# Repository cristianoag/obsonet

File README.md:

# Obsonet Reloaded

This is the GitHub repository to host all source files for the Obsonet Reloaded. 

The ObsoNET is the first network card created for the MSX. In 2004, the hardware designer Daniel Berdugo and software developer Nestor Soriano joined forces to create a cartridge to bring ETHERNET standard to the MSX line of computers. 

The cartridge is based on the Realtek RTL8019AS chip and uses a flash memory to host and execute a BIOS that allows the use of network commands from the Nextor operating system (compatible with MSXDOS). An EPROM stores basic configuration data for the RTL8019AS chip and a side connector is used to plug a network cable to your MSX. A GAL16VB is used to implement the logic required to activate and expose the cartridge to the computer.

The original version of the Obsonet was designed to fit a standard Konami cartridge case. The goal of this project is to create a new version of the cartridge that fits the standard Patola cartridge case available in Brazil as well as the standard Konami cases available from multiple vendors WW.

## Hardware 

### PCB

The files required to build the original version of the Obsonet are available [https://github.com/msx-solis/obsonet](here). You can download the gerber files and order from any PCB manufacturer.

I have created another version of the PCB that I called Obsonet Reloaded. The goal was to have the board fitting the standard Patola cartridge cases available in Brazil as well as the standard Konami cases available from multiple vendors WW.

|Front Side|Back Side|
|----------|---------|
|||
|||

### Bill of Materials

[Obsonet Reloaded Interactive BOM](https://htmlpreview.github.io/?https://github.com/cristianoag/obsonet/blob/main/hardware/bom/ibom.html)

| Reference | Value    | Description         | Package                  | Qtd | Link                                                                                         |
|-----------|----------|---------------------|---------------------------|-----|----------------------------------------------------------------------------------------------|
| C1-C4     | 100nF    | C-EUC1206K          | C1206                     | 4   | [Ali Express](https://s.click.aliexpress.com/e/_DmIukoX)                                    |
| C6        | 100 uF   | CPOL-EUE2.5-5       | E2.5-5                    | 1   | [Ali Express](https://s.click.aliexpress.com/e/_DmAGIvh)                                    |
| C7-C10    | 10nF     | C-EU050-030X075     | C050-030X075              | 4   | [Ali Express](https://s.click.aliexpress.com/e/_Dmqpgbd)                                    |
| CON2      | RJ45_F   | 555153-1             | 555153-1                  | 1   | [Ali Express](https://s.click.aliexpress.com/e/_c3jkvfpj) |
| IC1       | M29F400M | M29F400M             | SO44                      | 1   | [Ali Express](https://s.click.aliexpress.com/e/_c3iPiyOp)                                    |
| IC2       | 93C46_SOIC | AT93CX6SOIC08      | SOIC8 (you only need one DIP8 or SOIC8) | 1*  | [Ali Express](https://s.click.aliexpress.com/e/_De08kgX)                                    |
| IC3       | 74LS133  | 74LS133             | DIP16                     | 1   | [Ali Express](https://s.click.aliexpress.com/e/_c3DB6u1B)                                    |
| IC4       | RTL8019AS | RTL8019AS           | RTL8019AS                  | 1   | [Ali Express](https://s.click.aliexpress.com/e/_c3tW51wN)                                    |
| IC5       | 93C46_DIL | AT93CX6DIP8         | DIP8 (you only need one DIP8 or SOIC8) | 1*  |                                                                                              |
| IC6       | GAL16V8D | GAL16V8D             | DIP20                     | 1   | [Ali Express](https://s.click.aliexpress.com/e/_DB7dHhf)                                    |
| LED1      | Green    | Led 3mm              | LED3MM                    | 1   | [Ali Express](https://s.click.aliexpress.com/e/_DeGtXFv)                                    |
| LED2      | Orange   | Led 3mm              | LED3MM                    | 1   | [Ali Express](https://s.click.aliexpress.com/e/_DeGtXFv)                                    |
| Q1        | 20MHz    | HC49GW/HC49U         | HC49GW/J (or you can adapt the conventional HC49U) | 1   | [Ali Express](https://s.click.aliexpress.com/e/_c3AIkohX)                                    |
| R1,R4,R5  | 11K      | R-EU_R1206          | R1206                     | 3   | [Ali Express](https://s.click.aliexpress.com/e/_DF7KTEP)                                    |
| R2,R3     | 300R     | R-EU_R1206          | R1206                     | 2   | [Ali Express](https://s.click.aliexpress.com/e/_DF7KTEP)                                    |
| R6        | 27K      | R-EU_R1206          | R1206                     | 1   | [Ali Express](https://s.click.aliexpress.com/e/_DF7KTEP)                                    |
| R7        | 200R     | R-EU_R1206          | R1206                     | 1   | [Ali Express](https://s.click.aliexpress.com/e/_DF7KTEP)                                    |
| SW1       | SWITCH   | Microswitch 6×6     | 6×6 microswitch SMD       | 1   | [Ali Express](https://s.click.aliexpress.com/e/_DFJZR15)                                    |
| TF1       | 20F001N  | 20F001N             | DIL16/12                  | 1   | [Ali Express](https://s.click.aliexpress.com/e/_c3lk5as5)                                    |

## Software

On this repo you can find all software required to build and use the Obsonet Reloaded. There are also binary files with fixes for small issues we found during the project.

### BIOS

The BIOS is the software that runs on the flash memory of the cartridge. It is responsible for initializing the hardware and providing a set of functions to the Nextor operating system.

## Resources

I wrote an article providing more information on how to acquire components and build the new version of the cartridge. You can check it on my blog at [http://www.theretrohacker.com/2022/11/04/the-obsonet-cartridge-for-the-msx/](http://www.theretrohacker.com/2022/11/04/the-obsonet-cartridge-for-the-msx/).

I also have a video in Portuguese showing the board, software, issues we faced during the remodel project as well as showing how to use it to download and use software on your MSX. Please check it at [https://www.youtube.com/watch?v=Ph_3VFheo2I](https://www.youtube.com/watch?v=Ph_3VFheo2I)

## License

This work is licensed under a [Creative Commons Attribution-NonCommercial-ShareAlike 4.0 International License](http://creativecommons.org/licenses/by-nc-sa/4.0/).

Original version build by Daniel Berdugo and Nestor Soriano. Reloaded version by The Retro Hacker. 

* If you remix, transform, or build upon the material, you must distribute your contributions under the same license as the original.
* You may not use the material for commercial purposes.
* You must give appropriate credit, provide a link to the license, and indicate if changes were made. You may do so in any reasonable manner, but not in any way that suggests the licensor endorses you or your use.

**ATTENTION**

This project was made for the retro community and not for commercial purposes. So only retro hardware forums and individual people can build this project.

THE SALE OF ANY PART OF THIS PROJECT WITHOUT EXPRESS AUTHORIZATION IS PROHIBITED!

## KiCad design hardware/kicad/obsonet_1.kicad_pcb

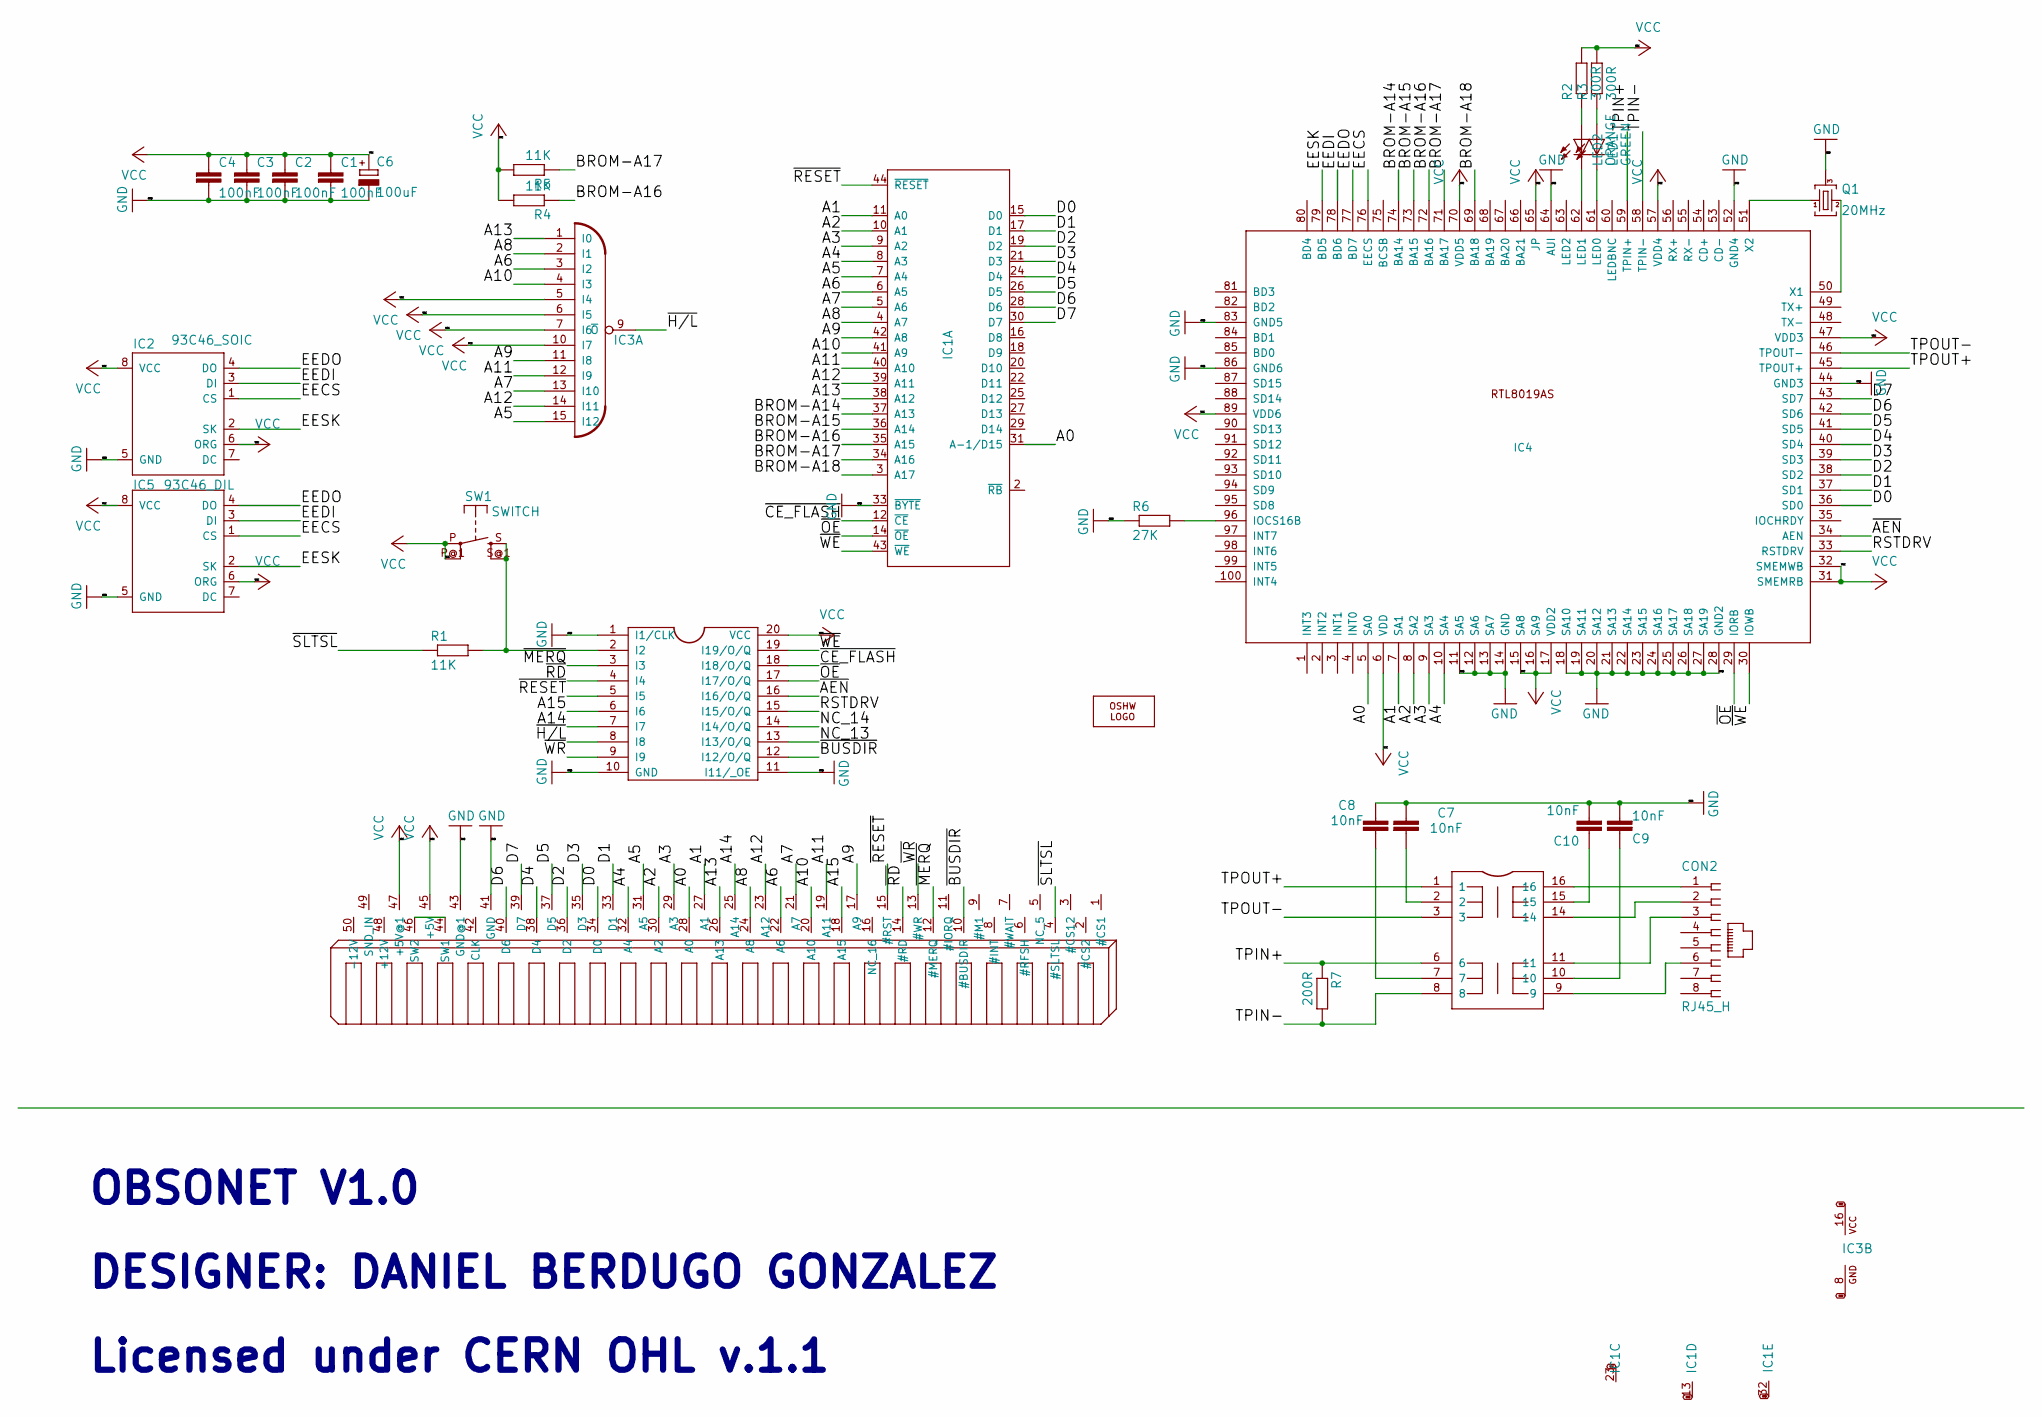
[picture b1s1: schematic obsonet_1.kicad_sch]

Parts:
C1, C2, C3, C4: 100nF; C1206K
C6: 100uF; E2,5-5
C7, C8, C9, C10: 10nF; C050-030X075
CON1: CART_BOARD; MSXCART
CON2: RJ45_H; 555153-1
IC1: M29F400M; SO44
IC2: 93C46_SOIC; SOIC8
IC3: 74HC133; DIP16
IC4: RTL8019AS
IC5: 93C46_DIL; DIP8
IC6: GAL16V8D; DIL20_SQUARE_1.5MM
LED1: GREEN; LED3MM
LED2: ORANGE; LED3MM
LOGO1: OSHW_LOGO_FILLX0500-NT; OSHW_FILLX500_NOTEXT
Q1: 20MHz; HC49GW
R1, R4, R5: 11K; R1206
R2, R3: 300R; R1206
R6: 27K; R1206
R7: 200R; R1206
SW1: SWITCH; MICROPULSADOR_6X6
TF1: 20F001N; DIL16_12

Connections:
/A0: CON1.28 (A0), IC1.31 (A-1/D15), IC4.5 (SA0)
/A1: CON1.27 (A1), IC1.11 (A0), IC4.7 (SA1)
/A2: CON1.30 (A2), IC1.10 (A1), IC4.8 (SA2)
/A3: CON1.29 (A3), IC1.9 (A2), IC4.9 (SA3)
/A4: CON1.32 (A4), IC1.8 (A3), IC4.10 (SA4)
/A5: CON1.31 (A5), IC1.7 (A4), IC3.15 (I12)
/A6: CON1.22 (A6), IC1.6 (A5), IC3.3 (I2)
/A7: CON1.21 (A7), IC1.5 (A6), IC3.13 (I10)
/A8: CON1.24 (A8), IC1.4 (A7), IC3.2 (I1)
/A9: CON1.17 (A9), IC1.42 (A8), IC3.11 (I8)
/A10: CON1.20 (A10), IC1.41 (A9), IC3.4 (I3)
/A11: CON1.19 (A11), IC1.40 (A10), IC3.12 (I9)
/A12: CON1.23 (A12), IC1.39 (A11), IC3.14 (I11)
/A13: CON1.26 (A13), IC1.38 (A12), IC3.1 (I0)
/A14: CON1.25 (A14), IC6.7 (I7)
/A15: CON1.18 (A15), IC6.6 (I6)
/BROM-A14: IC1.37 (A13), IC4.74 (BA14)
/BROM-A15: IC1.36 (A14), IC4.73 (BA15)
/BROM-A16: IC1.35 (A15), IC4.72 (BA16), R4.1
/BROM-A17: IC1.34 (A16), IC4.71 (BA17), R5.1
/BROM-A18: IC1.3 (A17), IC4.69 (BA18)
/D0: CON1.34 (D0), IC1.15 (D0), IC4.36 (SD0)
/D1: CON1.33 (D1), IC1.17 (D1), IC4.37 (SD1)
/D2: CON1.36 (D2), IC1.19 (D2), IC4.38 (SD2)
/D3: CON1.35 (D3), IC1.21 (D3), IC4.39 (SD3)
/D4: CON1.38 (D4), IC1.24 (D4), IC4.40 (SD4)
/D5: CON1.37 (D5), IC1.26 (D5), IC4.41 (SD5)
/D6: CON1.40 (D6), IC1.28 (D6), IC4.42 (SD6)
/D7: CON1.39 (D7), IC1.30 (D7), IC4.43 (SD7)
/EECS: IC2.1 (CS), IC4.76 (EECS), IC5.1 (CS)
/EEDI: IC2.3 (DI), IC4.78 (BD6), IC5.3 (DI)
/EEDO: IC2.4 (DO), IC4.77 (BD7), IC5.4 (DO)
/EESK: IC2.2 (SK), IC4.79 (BD5), IC5.2 (SK)
/NC_13: IC6.13 (I13/O/Q)
/NC_14: IC6.14 (I14/O/Q)
/RSTDRV: IC4.33 (RSTDRV), IC6.15 (I15/O/Q)
/TPIN+: IC4.59 (TPIN+), R7.1, TF1.6
/TPIN-: IC4.58 (TPIN-), R7.2, TF1.8
/TPOUT+: IC4.45 (TPOUT+), TF1.1
/TPOUT-: IC4.46 (TPOUT-), TF1.3
/~AEN: IC4.34 (AEN), IC6.16 (I16/O/Q)
/~BUSDIR: CON1.10 (#BUSDIR), IC6.12 (I12/O/Q)
/~CE_FLASH: IC1.12 (~CE), IC6.18 (I18/O/Q)
/~H/L: IC3.9 (~O), IC6.8 (I8)
/~MERQ: CON1.12 (#MERQ), IC6.3 (I3)
/~OE: IC1.14 (~OE), IC4.29 (IORB), IC6.17 (I17/O/Q)
/~RD: CON1.14 (#RD), IC6.4 (I4)
/~RESET: CON1.15 (#RST), IC1.44 (~RESET), IC6.5 (I5)
/~SLTSL: CON1.4 (#SLTSL), R1.1
/~WE: IC1.43 (~WE), IC4.30 (IOWB), IC6.19 (I19/O/Q)
/~WR: CON1.13 (#WR), IC6.9 (I9)
GND: C1.2, C2.2, C3.2, C4.2, C6.-, C7.1, C8.1, C9.2, C10.2, CON1.41 (GND), CON1.43 (GND@1), IC1.13 (GND), IC1.32 (GND), IC1.33 (~BYTE), IC2.5 (GND), IC3.8 (GND), IC4.11 (SA5), IC4.12 (SA6), IC4.13 (SA7), IC4.14 (GND), IC4.18 (SA10), IC4.19 (SA11), IC4.20 (SA12), IC4.21 (SA13), IC4.22 (SA14), IC4.23 (SA15), IC4.24 (SA16), IC4.25 (SA17), IC4.26 (SA18), IC4.27 (SA19), IC4.28 (GND2), IC4.44 (GND3), IC4.52 (GND4), IC4.64 (AUI), IC4.83 (GND5), IC4.86 (GND6), IC5.5 (GND), IC6.1 (I1/CLK), IC6.10 (GND), IC6.11 (I11/_OE), Q1.3, R6.1
unnamed: C7.2, TF1.2
unnamed: C8.2, TF1.7
unnamed: C9.1, TF1.10
unnamed: C10.1, TF1.15
unnamed: CON1.44 (SW1), CON1.46 (SW2)
unnamed: CON2.1, TF1.16
unnamed: CON2.2, TF1.14
unnamed: CON2.3, TF1.11
unnamed: CON2.6, TF1.9
unnamed: IC4.50 (X1), Q1.2
unnamed: IC4.51 (X2), Q1.1
unnamed: IC4.61 (LED0), LED1.K (C)
unnamed: IC4.62 (LED1), LED2.K (C)
unnamed: IC4.96 (IOCS16B), R6.2
unnamed: IC6.2 (I2), R1.2, SW1.S, SW1.S@1
unnamed: LED1.A, R3.1
unnamed: LED2.A, R2.1
VCC: C1.1, C2.1, C3.1, C4.1, C6.+, CON1.45 (+5V), CON1.47 (+5V@1), IC1.23 (VCC), IC2.6 (ORG), IC2.8 (VCC), IC3.5 (I4), IC3.6 (I5), IC3.7 (I6), IC3.10 (I7), IC3.16 (VCC), IC4.6 (VDD), IC4.15 (SA8), IC4.16 (SA9), IC4.17 (VDD2), IC4.31 (SMEMRB), IC4.32 (SMEMWB), IC4.47 (VDD3), IC4.57 (VDD4), IC4.65 (JP), IC4.70 (VDD5), IC4.89 (VDD6), IC5.6 (ORG), IC5.8 (VCC), IC6.20 (VCC), R2.2, R3.2, R4.2, R5.2, SW1.P, SW1.P@1

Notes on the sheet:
DESIGNER: DANIEL BERDUGO GONZALEZ
OBSONET V1.0
Licensed under CERN OHL v.1.1

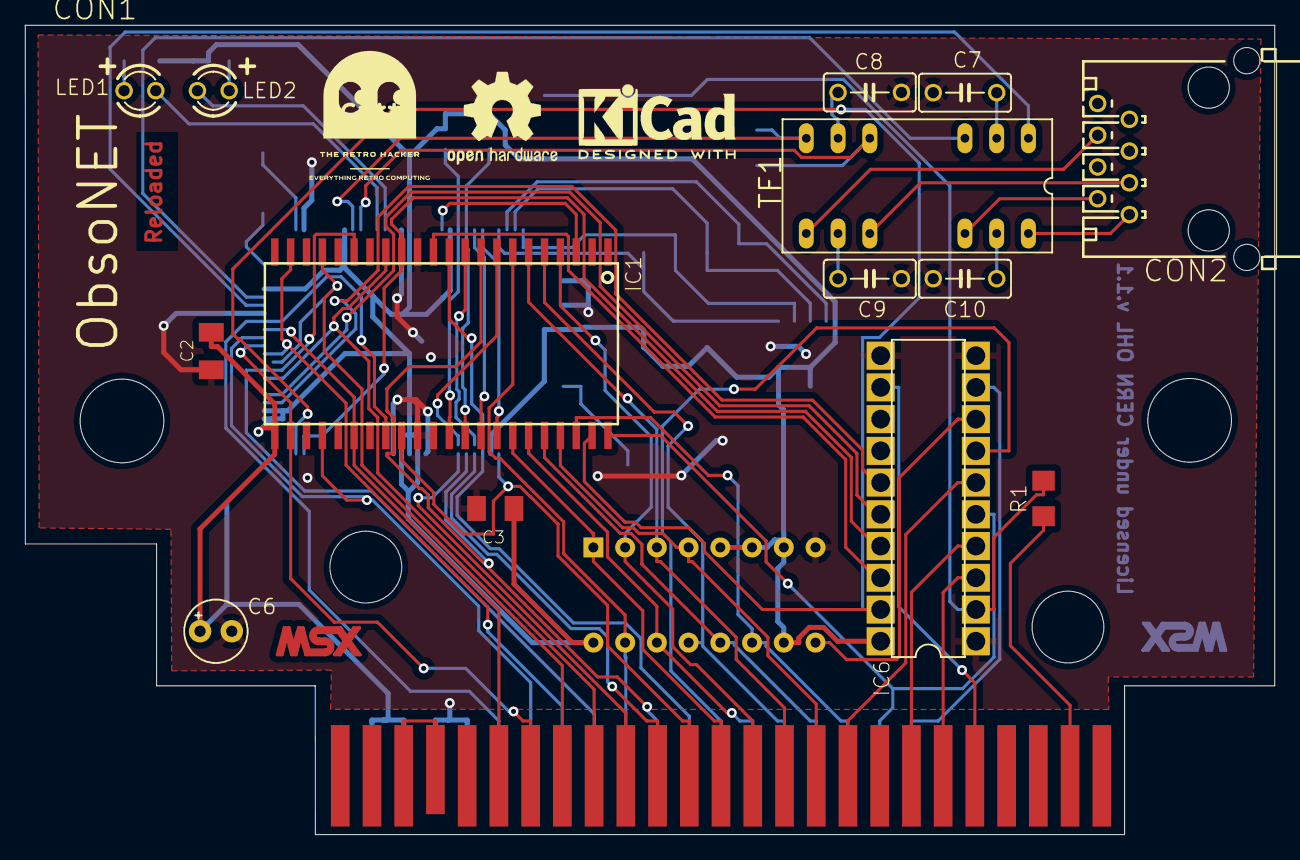
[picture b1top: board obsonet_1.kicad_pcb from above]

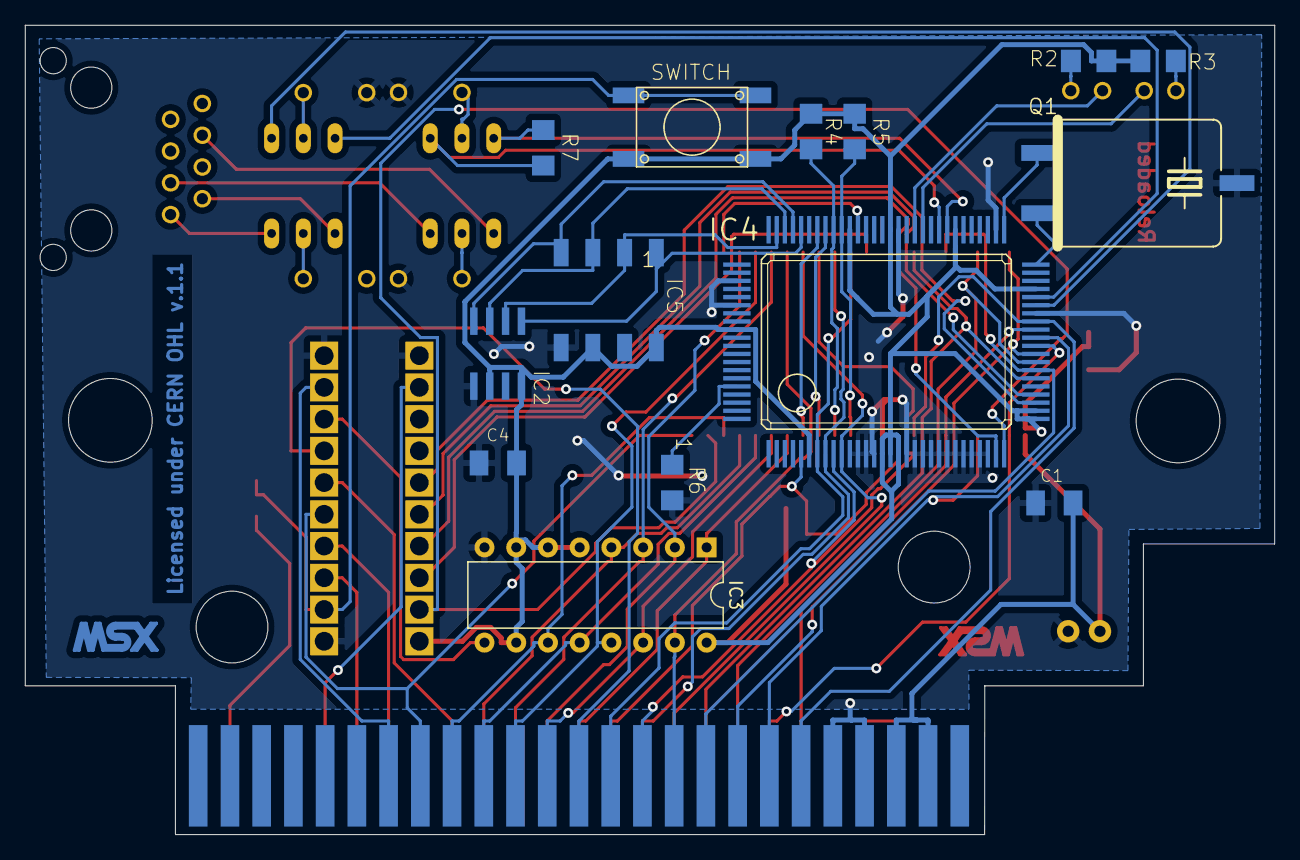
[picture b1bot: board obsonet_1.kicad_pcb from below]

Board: 2 copper layers, 100.0 x 64.8 mm, 32 parts (15 on the bottom side), 68 nets.

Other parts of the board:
U$1, U$2: LOGO_MSX
U$4: LOGO_OBSONET

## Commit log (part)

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2022-12-15 Initial load
2022-12-15 Readme and additional images
2022-12-15 Fixes on the readme
2022-12-15 Resources added
2023-01-02 including 3d printer cases
2024-03-03 Updated licensing and README
2024-12-17 new labels
2024-12-17 new labels, readme.md update, hardware folder organization
2024-12-17 readme.md update
2025-10-05 Guides
2025-10-05 docs: add Japanese translation of Quick Guide (ja)
2025-10-05 fixed the double-dot filename
